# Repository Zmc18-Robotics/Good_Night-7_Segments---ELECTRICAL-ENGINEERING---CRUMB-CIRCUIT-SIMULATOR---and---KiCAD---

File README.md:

# Good Night 7 Segments --- ELECTRICAL-ENGINEERING --- CRUMB-CIRCUIT-SIMULATOR --- and --- KiCAD ---
Just simple 7 segments and some LED's that shows Good Night🌙

---

# Here the pictures :

---

# Electrical Circuit :

---

# Description

Some 7 Segments used in this project, and some LED's art, showed "Good Night" and Moon Art LED

used to be the knowledge of 7 Segments systems, Seems complex but it's actually easy, It's just LED but it in the box of Numbers / Alphabet. Make sure the voltage is 5.4V

Here the materials :
- Breadboard x8
- Arduino Nano x1
- LED pin x121
- Resistor 220Ω x10
- Resistor 40Ω x2
- Resistor 10000Ω x1
- SPST Switch x1
- Power Supply x1
- Capacitor 33µF x1

---

ELECTRICITY!✨~ ☆*: .｡. o(≧▽≦)o .｡.:*☆

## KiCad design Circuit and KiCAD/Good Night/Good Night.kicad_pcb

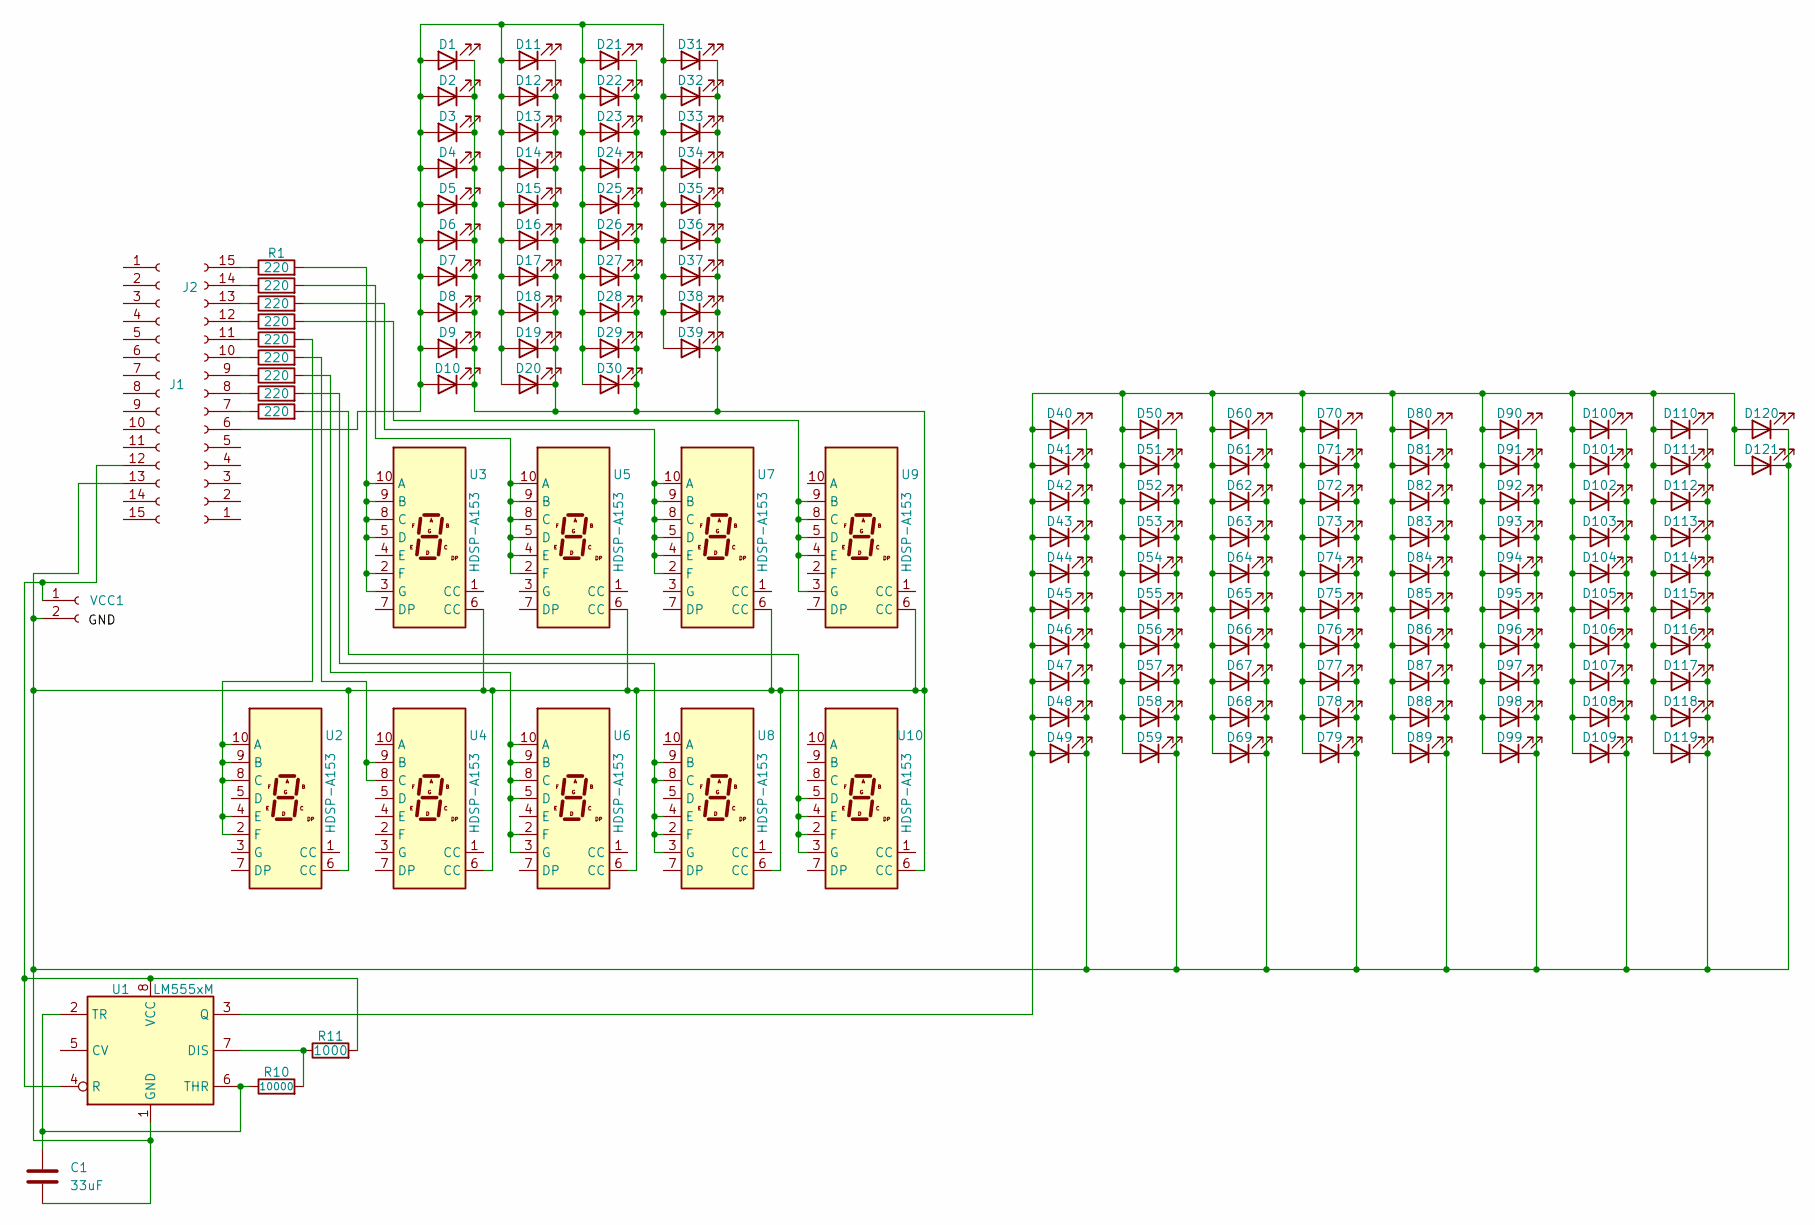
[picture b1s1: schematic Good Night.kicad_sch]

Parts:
C1: 33uF; CP_Elec_6.3x5.4
D1, D2, D3, D4, D5, D6, D7, D8, D9, D10, D11, D12, D13, D14, D15, D16, D17, D18, D19, D20, D21, D22, D23, D24, D25, D26, D27, D28, D29, D30, D31, D32, D33, D34, D35, D36, D37, D38, D39: LED; LED_D5.0mm
D40, D41, D42, D43, D44, D45, D46, D47, D48, D49, D50, D51, D52, D53, D54, D55, D56, D57, D58, D59, D60, D61, D62, D63, D64, D65, D66, D67, D68, D69, D70, D71, D72, D73, D74, D75, D76, D77, D78, D79, D80, D81, D82, D83, D84, D85, D86, D87, D88, D89, D90, D91, D92, D93, D94, D95, D96, D97, D98, D99, D100, D101, D102, D103, D104, D105, D106, D107, D108, D109, D110, D111, D112, D113, D114, D115, D116, D117, D118, D119, D120, D121: LED; LED_0805_2012Metric
J1, J2: Conn_01x15_Socket; PinSocket_1x15_P2.54mm_Vertical
R1, R2, R3, R4, R5, R6, R7, R8, R9: 220; R_0805_2012Metric
R10: 10000; R_0805_2012Metric
R11: 1000; R_0805_2012Metric
U1: LM555xM; SOIC-8_3.9x4.9mm_P1.27mm
U2, U3, U4, U5, U6, U7, U8, U9, U10: HDSP-A153; HDSP-A151
VCC1: Conn_01x02_Socket; PinSocket_1x02_P2.54mm_Vertical

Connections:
unnamed: D1.2 (A), D2.2 (A), D3.2 (A), D4.2 (A), D5.2 (A), D6.2 (A), D7.2 (A), D8.2 (A), D9.2 (A), D10.2 (A), D11.2 (A), D12.2 (A), D13.2 (A), D14.2 (A), D15.2 (A), D16.2 (A), D17.2 (A), D18.2 (A), D19.2 (A), D20.2 (A), D21.2 (A), D22.2 (A), D23.2 (A), D24.2 (A), D25.2 (A), D26.2 (A), D27.2 (A), D28.2 (A), D29.2 (A), D30.2 (A), D31.2 (A), D32.2 (A), D33.2 (A), D34.2 (A), D35.2 (A), D36.2 (A), D37.2 (A), D38.2 (A), D39.2 (A), J2.6
unnamed 1: C1.2, D1.1 (K), D2.1 (K), D3.1 (K), D4.1 (K), D5.1 (K), D6.1 (K), D7.1 (K), D8.1 (K), D9.1 (K), D10.1 (K), D11.1 (K), D12.1 (K), D13.1 (K), D14.1 (K), D15.1 (K), D16.1 (K), D17.1 (K), D18.1 (K), D19.1 (K), D20.1 (K), D21.1 (K), D22.1 (K), D23.1 (K), D24.1 (K), D25.1 (K), D26.1 (K), D27.1 (K), D28.1 (K), D29.1 (K), D30.1 (K), D31.1 (K), D32.1 (K), D33.1 (K), D34.1 (K), D35.1 (K), D36.1 (K), D37.1 (K), D38.1 (K), D39.1 (K), D40.1 (K), D41.1 (K), D42.1 (K), D43.1 (K), D44.1 (K), D45.1 (K), D46.1 (K), D47.1 (K), D48.1 (K), D49.1 (K), D50.1 (K), D51.1 (K), D52.1 (K), D53.1 (K), D54.1 (K), D55.1 (K), D56.1 (K), D57.1 (K), D58.1 (K), D59.1 (K), D60.1 (K), D61.1 (K), D62.1 (K), D63.1 (K), D64.1 (K), D65.1 (K), D66.1 (K), D67.1 (K), D68.1 (K), D69.1 (K), D70.1 (K), D71.1 (K), D72.1 (K), D73.1 (K), D74.1 (K), D75.1 (K), D76.1 (K), D77.1 (K), D78.1 (K), D79.1 (K), D80.1 (K), D81.1 (K), D82.1 (K), D83.1 (K), D84.1 (K), D85.1 (K), D86.1 (K), D87.1 (K), D88.1 (K), D89.1 (K), D90.1 (K), D91.1 (K), D92.1 (K), D93.1 (K), D94.1 (K), D95.1 (K), D96.1 (K), D97.1 (K), D98.1 (K), D99.1 (K), D100.1 (K), D101.1 (K), D102.1 (K), D103.1 (K), D104.1 (K), D105.1 (K), D106.1 (K), D107.1 (K), D108.1 (K), D109.1 (K), D110.1 (K), D111.1 (K), D112.1 (K), D113.1 (K), D114.1 (K), D115.1 (K), D116.1 (K), D117.1 (K), D118.1 (K), D119.1 (K), D120.1 (K), D121.1 (K), J1.13, U1.1 (GND), U2.6 (CC), U3.6 (CC), U4.6 (CC), U5.6 (CC), U6.6 (CC), U7.6 (CC), U8.6 (CC), U9.6 (CC), U10.6 (CC), VCC1.2; also elsewhere on the board
unnamed: D40.2 (A), D41.2 (A), D42.2 (A), D43.2 (A), D44.2 (A), D45.2 (A), D46.2 (A), D47.2 (A), D48.2 (A), D49.2 (A), D50.2 (A), D51.2 (A), D52.2 (A), D53.2 (A), D54.2 (A), D55.2 (A), D56.2 (A), D57.2 (A), D58.2 (A), D59.2 (A), D60.2 (A), D61.2 (A), D62.2 (A), D63.2 (A), D64.2 (A), D65.2 (A), D66.2 (A), D67.2 (A), D68.2 (A), D69.2 (A), D70.2 (A), D71.2 (A), D72.2 (A), D73.2 (A), D74.2 (A), D75.2 (A), D76.2 (A), D77.2 (A), D78.2 (A), D79.2 (A), D80.2 (A), D81.2 (A), D82.2 (A), D83.2 (A), D84.2 (A), D85.2 (A), D86.2 (A), D87.2 (A), D88.2 (A), D89.2 (A), D90.2 (A), D91.2 (A), D92.2 (A), D93.2 (A), D94.2 (A), D95.2 (A), D96.2 (A), D97.2 (A), D98.2 (A), D99.2 (A), D100.2 (A), D101.2 (A), D102.2 (A), D103.2 (A), D104.2 (A), D105.2 (A), D106.2 (A), D107.2 (A), D108.2 (A), D109.2 (A), D110.2 (A), D111.2 (A), D112.2 (A), D113.2 (A), D114.2 (A), D115.2 (A), D116.2 (A), D117.2 (A), D118.2 (A), D119.2 (A), D120.2 (A), D121.2 (A), U1.3 (Q)
unnamed 3: J1.12, R11.2, U1.4 (R), U1.8 (VCC), VCC1.1; also elsewhere on the board
unnamed: J2.7, R9.1
unnamed: J2.8, R8.1
unnamed: J2.9, R7.1
unnamed: J2.10, R6.1
unnamed: J2.11, R5.1
unnamed: J2.12, R4.1
unnamed: J2.13, R3.1
unnamed: J2.14, R2.1
unnamed: J2.15, R1.1
unnamed: R10.2, R11.1, U1.7 (DIS)
unnamed: C1.1, R10.1, U1.2 (TR), U1.6 (THR)
unnamed: R5.2, U2.2 (F), U2.4 (E), U2.8 (C), U2.9 (B), U2.10 (A)
unnamed: R1.2, U3.2 (F), U3.3 (G), U3.5 (D), U3.8 (C), U3.9 (B), U3.10 (A)
unnamed: R6.2, U4.8 (C), U4.9 (B)
unnamed: R2.2, U5.2 (F), U5.4 (E), U5.5 (D), U5.8 (C), U5.9 (B), U5.10 (A)
unnamed: R7.2, U6.2 (F), U6.3 (G), U6.5 (D), U6.8 (C), U6.9 (B), U6.10 (A)
unnamed: R3.2, U7.2 (F), U7.4 (E), U7.5 (D), U7.8 (C), U7.9 (B), U7.10 (A)
unnamed: R8.2, U8.2 (F), U8.3 (G), U8.4 (E), U8.8 (C), U8.9 (B)
unnamed: R4.2, U9.3 (G), U9.4 (E), U9.5 (D), U9.8 (C), U9.9 (B)
unnamed: R9.2, U10.2 (F), U10.3 (G), U10.4 (E), U10.5 (D)

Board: 2 copper layers, 146 parts (0 on the bottom side), 24 nets, no tracks yet.

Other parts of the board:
VCC: GND; PinSocket_1x02_P2.54mm_Vertical

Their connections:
unnamed 1: VCC.2; also elsewhere on the board
unnamed 3: VCC.1; also elsewhere on the board

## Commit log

2026-02-25 Fix power supply quantity in README
2026-05-10 Circuit and description
